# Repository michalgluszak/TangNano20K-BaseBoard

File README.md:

# Tang Nano 20K Expansion Baseboard

## Project Status

**PCB design prototype — Not fabricated or hardware-tested.**

The schematic and PCB layout were designed in KiCad. The board has not been manufactured or physically tested, so its functionality has not been verified on real hardware. The design may require further revisions before fabrication.

## About the Project

The **Tang Nano 20K Expansion Baseboard** is a custom PCB expansion board designed to make learning and prototyping digital circuits easier using Hardware Description Languages (HDL), such as Verilog and VHDL.

The idea for this project came from a desire to test written code in practice. Commercial evaluation platforms, like Basys 3 or boards based on Artix 7 chips, are relatively expensive. As an alternative, I chose the Tang Nano 20K FPGA development board, which offers great features at a very affordable price (around 120 PLN). To make working with this module easier, I designed a dedicated expansion board.

A huge advantage of this solution is its modularity – the Tang Nano 20K module is not soldered permanently. It is placed in pin headers, so you can take it out anytime and use it in another project directly on a breadboard.

## Features

* **Budget-friendly alternative:** A full evaluation environment for learning FPGA at a fraction of the cost of commercial solutions.
* **Modularity (Plug & Play):** The ability to easily remove the Tang Nano chip and use it outside the motherboard.
* **Data visualization:** Built-in **4 LEDs**, a **4-digit 7-segment display** (perfect for testing things like BCD decoders or counters), and support for an **OLED screen**, which makes viewing results and fast code debugging much easier.
* **Input interface:** The board has **4 push-buttons** and **4 slide switches**, which are necessary for manually setting logic states (0/1) and testing state machines.
* **Expandability (PMOD):** An integrated PMOD standard connector allows you to easily connect a wide range of external peripheral modules, such as sensors (e.g., temperature), converters, or additional interfaces.

## PCB Technical Specifications

During the PCB design in KiCad, I focused on organizing signal routing, maintaining ground planes, and applying via stitching to support signal integrity and reduce potential electromagnetic interference (EMI).

* **Board dimensions:** 100 mm x 90 mm.
* **Signal trace width (0.25 mm):** Routed tightly and compactly to minimize their length and delays.
* **Power trace width (0.6 mm):** Wider traces were used for power distribution to reduce resistance and voltage drops.
* **Two-layer PCB:** Most signal and power traces were routed on the top layer, with only one trace routed on the bottom layer to minimize interruptions to the ground plane.
* **Ground Planes:** GND copper pours were added on both PCB layers to provide return paths for signals and improve grounding.
* **Via Stitching:** Multiple stitching vias were used to connect the top and bottom GND copper pours, with the aim of maintaining ground continuity and reducing return-path impedance.

## Schematic

The schematic is divided into logical blocks: Tang Nano 20K Connectors, User LEDs, GPIO Expansion Headers, 4-Digit 7-Segment Display, Push Buttons, Slide Switches, and OLED Display (I2C).

## PCB Design

Below is a screenshot of the PCB layout showing the routing and via stitching structure.

**Top Layer:**

**Bottom Layer:**

## Bill of Materials (BOM)

To make the review and assembly of the board easier, I generated an interactive Bill of Materials (BOM). You can closely inspect the routing and component placement there.

👉 **[Open Interactive BOM](https://michalgluszak.github.io/TangNano20K-BaseBoard/Documentation/bom/ibom.html)**

---
*Project created in KiCad 10.0.*

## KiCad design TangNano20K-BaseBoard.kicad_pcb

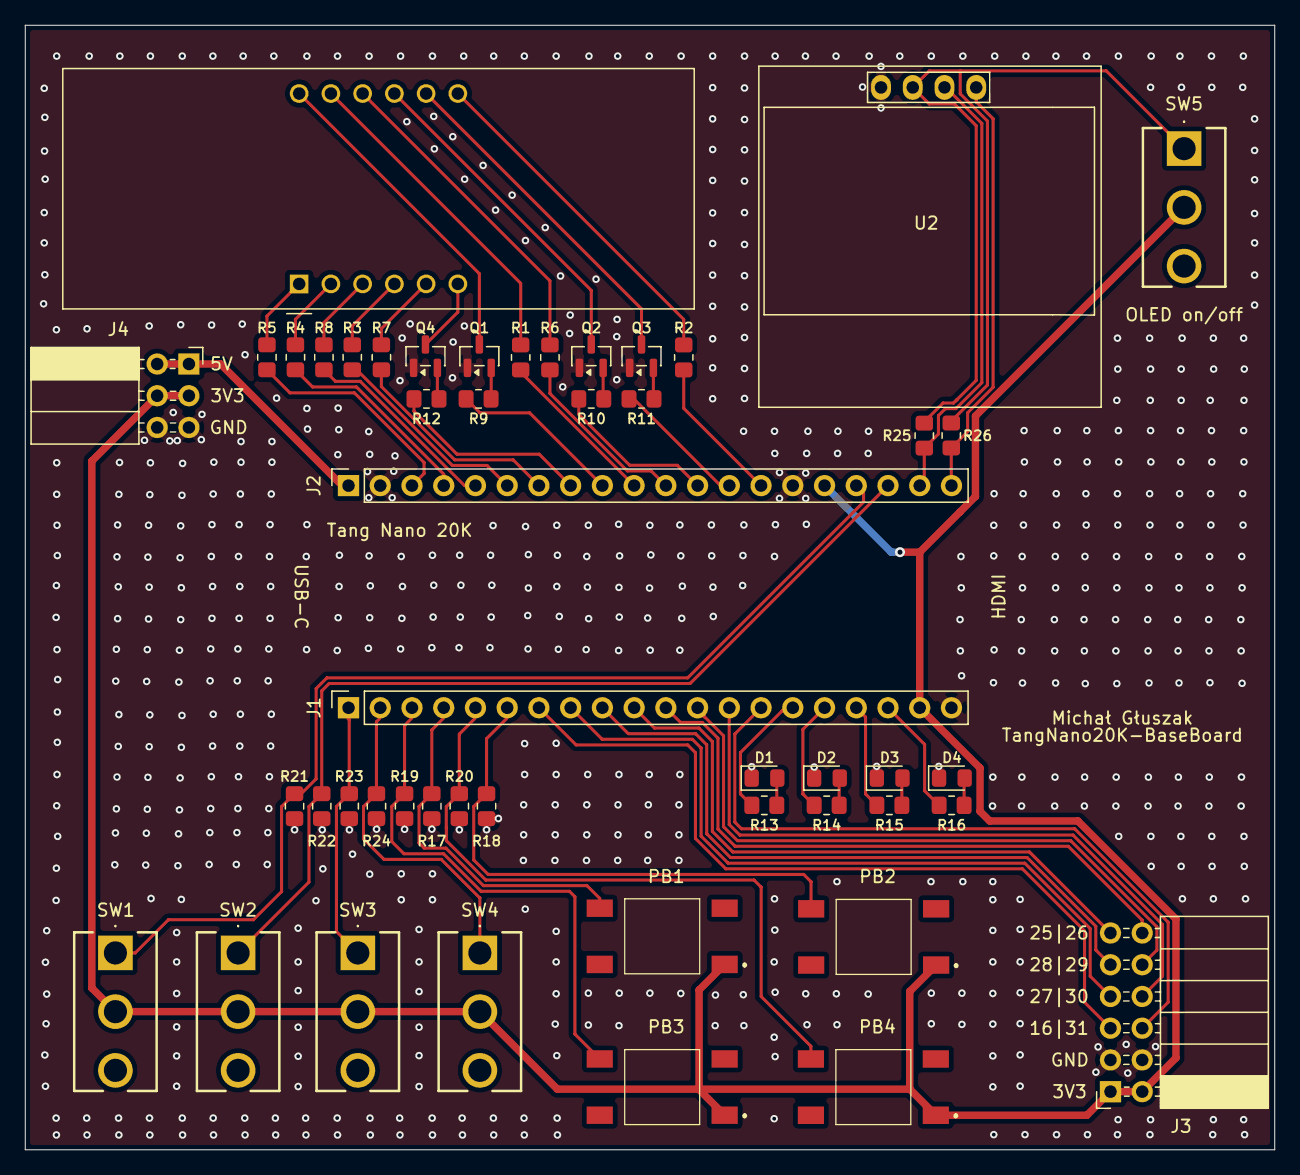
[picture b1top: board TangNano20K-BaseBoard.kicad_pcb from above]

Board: 2 copper layers, 100.0 x 90.0 mm, 49 parts (0 on the bottom side), 58 nets.

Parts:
D1, D2, D3, D4: LED; LED_0805_2012Metric_Pad1.15x1.40mm_HandSolder
J1, J2: Conn_01x20_Socket; PinSocket_1x20_P2.54mm_Vertical
J3: Conn_02x06_Odd_Even; PinSocket_2x06_P2.54mm_Horizontal
J4: Conn_02x03_Odd; PinSocket_2x03_P2.54mm_Horizontal
PB1, PB2, PB3, PB4: 1301.9315; 13019319
Q1, Q2, Q3, Q4: PN2222A; SOT-23
R1, R2, R3, R4, R5, R6, R7, R8: 220R; R_0805_2012Metric_Pad1.20x1.40mm_HandSolder
R9, R10, R11, R12, R13, R14, R15, R16: 330R; R_0805_2012Metric_Pad1.20x1.40mm_HandSolder
R17, R18, R19, R20, R21, R22, R23, R24, R25, R26: 10k; R_0805_2012Metric_Pad1.20x1.40mm_HandSolder
SW1, SW2, SW3, SW4, SW5: SW_SPDT_321; SL19121
U1: CC56-12EWA; CA56-12EWA
U2: SSD1306; 128x64OLED

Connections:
+3V3: J1.19, J2.16, J3.1, J3.2, J4.3, J4.4, PB1.1 (NO_1), PB2.1 (NO_1), PB3.1 (NO_1), PB4.1 (NO_1), SW1.2 (B), SW2.2 (B), SW3.2 (B), SW4.2 (B), SW5.2 (B)
+5V: J2.1, J4.1, J4.2
/15: J1.6, PB2.4 (COM_2), R18.2
/16: J1.7, J3.5
/17: J1.15, R13.1
/18: J1.18, R16.1
/19: J1.17, R15.1
/20: J1.16, R14.1
/25: J1.10, J3.11
/26: J1.11, J3.12
/27: J1.8, J3.7
/28: J1.9, J3.9
/29: J1.12, J3.10
/30: J1.13, J3.8
/31: J1.14, J3.6
/41: J2.6, R3.1
/42: J2.5, R8.1
/48: J2.10, R1.1
/49: J2.12, R10.2
/51: J2.9, R9.2
/52: J2.20, R26.1, U2.4 (SDA)
/53: J2.19, R25.2, U2.3 (SCL)
/54: J2.8, R12.2
/55: J2.11, R6.1
/56: J2.7, R7.1
/71: J2.18, R22.2, SW2.1 (C)
/72: J2.17, R21.2, SW1.1 (C)
/73: J1.1, R23.2, SW3.1 (C)
/74: J1.2, R24.2, SW4.1 (C)
/75: J1.3, PB3.4 (COM_2), R19.2
/76: J2.3, R5.1
/77: J1.5, PB4.4 (COM_2), R20.2
/79: J2.14, R2.1
/80: J2.4, R4.1
/85: J1.4, PB1.4 (COM_2), R17.2
/86: J2.13, R11.2
/CC1: Q1.3 (C), U1.12 (CC1)
/CC2: Q2.3 (C), U1.9 (CC2)
/CC3: Q3.3 (C), U1.8 (CC3)
/CC4: Q4.3 (C), U1.6 (CC4)
/DPX: R8.2, U1.3 (DPX)
/a: R1.2, U1.11 (a)
/b: R2.2, U1.7 (b)
/c: R3.2, U1.4 (c)
/d: R4.2, U1.2 (d)
/e: R5.2, U1.1 (e)
/f: R6.2, U1.10 (f)
/g: R7.2, U1.5 (g)
GND: D1.1 (K), D2.1 (K), D3.1 (K), D4.1 (K), J1.20, J2.2, J2.15, J3.3, J3.4, J4.5, J4.6, Q1.1 (E), Q2.1 (E), Q3.1 (E), Q4.1 (E), R17.1, R18.1, R19.1, R20.1, R21.1, R22.1, R23.1, R24.1, U2.1 (GND)
unnamed: D1.2 (A), R13.2
unnamed: D2.2 (A), R14.2
unnamed: D3.2 (A), R15.2
unnamed: D4.2 (A), R16.2
unnamed: Q1.2 (B), R9.1
unnamed: Q2.2 (B), R10.1
unnamed: Q3.2 (B), R11.1
unnamed: Q4.2 (B), R12.1
unnamed: R25.1, R26.2, SW5.1 (C), U2.2 (VCC)

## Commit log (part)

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2026-06-27 Add .gitignore file
2026-06-27 Add all files
2026-06-27 Add electronic schematic
2026-06-27 Add footprint for electronic element
2026-06-27 Update schematic, add new symbol, footprint and 3d model
2026-06-27 Update schematic and start design pcb layout
2026-06-27 Update SW1, SW2, SW3, SW4, SW5
2026-06-28 Update schematic and pcb
2026-06-28 Big Update
